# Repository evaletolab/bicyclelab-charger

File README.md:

# 85-110W single output battery charger

This is an opensource lithium-ion battery charger that use laptop power adapter as input.
* Further reading regarding [the bicycle manager](https://github.com/evaletolab/bicyclelab-manager)?

## Features

1. boost input from 18.5V - 4.7A to 42V (or 47.2V) with ~95% of efficiency 
2. stage charging; current control then voltage control
3. full protections: Short circuit / Overload / Over voltage / Over temperature
4. 1 LED indicator for charging status
5. BMS features; Balancing charge on each cell [TODO]
6. custom number of serial cells 5..12
7. small size, only 30x90x8mm

## The result

## Power stage (battery charge)

This if the fourth prototype release. The purpose of this board is to manage the charge  
of a 10/11 serial lithium-ion cell with an input given by a laptop ac adapter (currently the apple magsafe1 85W). 
The software is mainly a PID control based on the MAX_POWER for the fast charge and the BATTERY_VOLTAGE for 
the constant charge. The size of the board is about 30x90mm

## Cell balancing and protection
This project is targeted for each individual cell. The purpose of this project is to make a simple cascading 
module to manage over/under voltage/temperatur for each cell. The first prototype is still not available for testing. 

1. an overvoltage measurement is triggering a passive balancing for the cell
2. TODO - implement an isolated one wire communication to broadcast,
  * undervoltage signal
  * over temperature signal
 
## License
GPL3

Copyright (c) 2012 Olivier Evalet (http://evaletolab.ch/)

Permission is hereby granted, free of charge, to any person obtaining a copy
of this software and associated documentation files (the “Software”), to deal
in the Software without restriction, including without limitation the rights
to use, copy, modify, merge, publish, distribute, sublicense, and/or sell
copies of the Software, and to permit persons to whom the Software is
furnished to do so, subject to the following conditions:

The above copyright notice and this permission notice shall be included in
all copies or substantial portions of the Software.

THE SOFTWARE IS PROVIDED “AS IS”, WITHOUT WARRANTY OF ANY KIND, EXPRESS OR
IMPLIED, INCLUDING BUT NOT LIMITED TO THE WARRANTIES OF MERCHANTABILITY,
FITNESS FOR A PARTICULAR PURPOSE AND NONINFRINGEMENT. IN NO EVENT SHALL THE
AUTHORS OR COPYRIGHT HOLDERS BE LIABLE FOR ANY CLAIM, DAMAGES OR OTHER
LIABILITY, WHETHER IN AN ACTION OF CONTRACT, TORT OR OTHERWISE, ARISING FROM,
OUT OF OR IN CONNECTION WITH THE SOFTWARE OR THE USE OR OTHER DEALINGS IN
THE SOFTWARE.

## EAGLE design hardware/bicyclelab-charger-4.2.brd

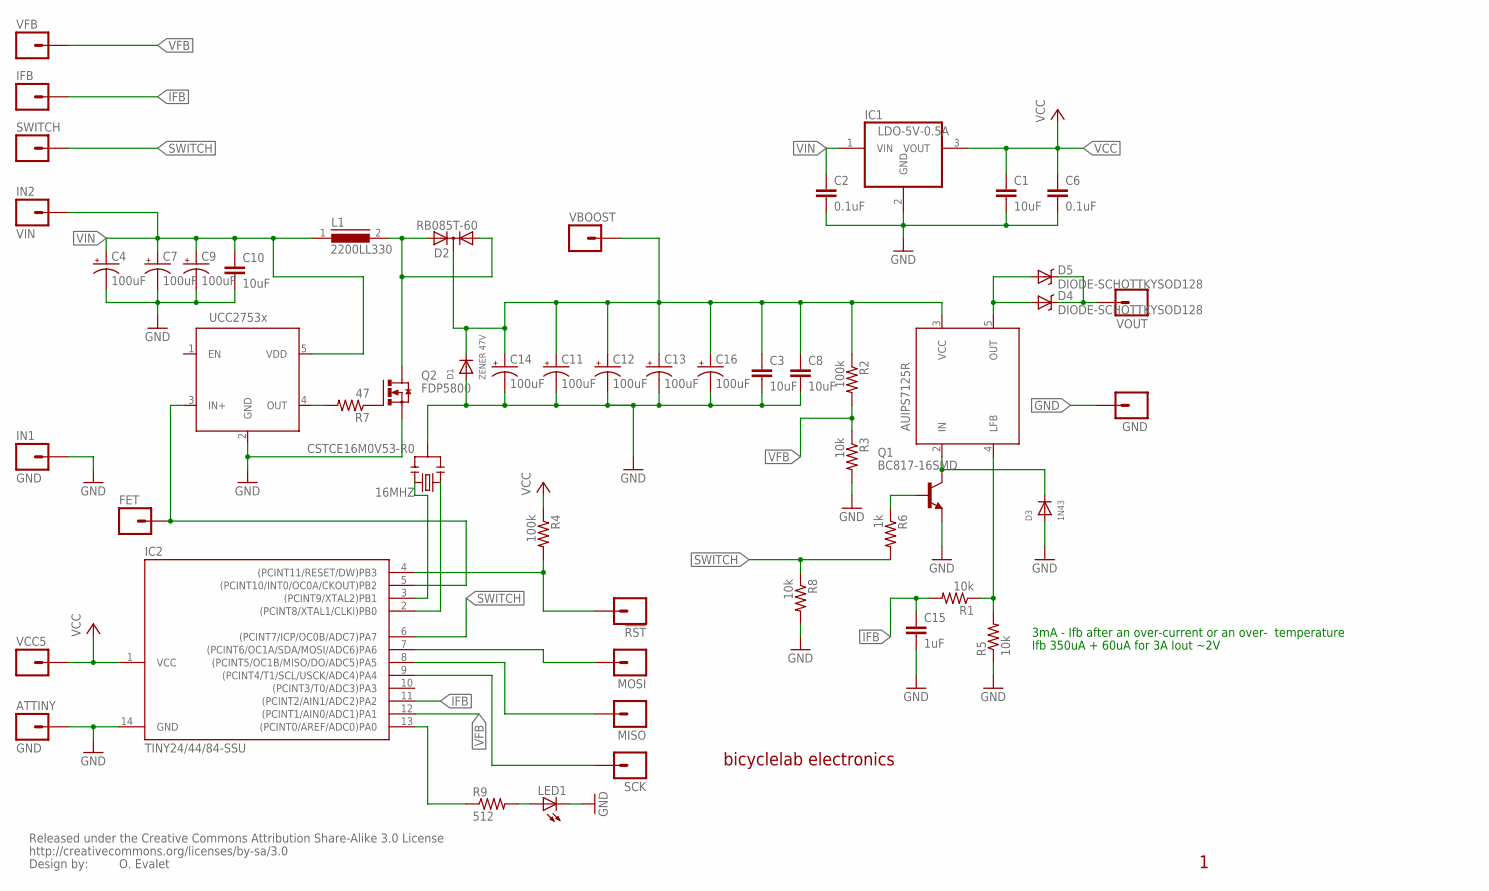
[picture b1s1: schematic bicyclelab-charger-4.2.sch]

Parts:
16MHZ: CSTCE16M0V53-R0; RESONATOR-SMD
!RST: M01SMDNS; 1X01NS
ATTINY: GND; 1X01NS
C1: 10uF; 0805
C2, C6: 0.1uF; 0805
C3, C8, C10: 10uF; 1210
C4, C7, C9, C11, C12, C13, C14, C16: 100uF; PANASONIC_D
C15: 1uF; 0805
D1: ZENER 47V; SOD-123
D2: RB085T-60; TO220AB
D3: 1N43; SOD-123
D4, D5: DIODE-SCHOTTKYSOD128; SOD-128
FET: M01SMDNS; 1X01NS
GND: M01SMDNS; 1X01NS
IC1: LDO-5V-0.5A; SOT223
IC2: TINY24/44/84-SSU; SOIC14
IFB: M01SMDNS; 1X01NS
IN1: GND; 1X01NS
IN2: VIN; 1X01
L1: 2200LL330; DR175
LED1: LEDCHIP-LED0805; CHIP-LED0805
MISO: M01SMDNS; 1X01NS
MOSI: M01SMDNS; 1X01NS
Q1: BC817-16SMD; SOT23-BEC
Q2: FDP5800; TO220AH
R1, R3, R5, R8: 10k; 0805
R2, R4: 100k; 0805
R6: 1k; 0805
R7: 47; 0805
R9: 512; 0805
SCK: M01SMDNS; 1X01NS
SWITCH: M01SMDNS; 1X01NS
U$1: UCC2753XSOT23-6; SOT23-6
U$5: CREATIVE_COMMONS
U$8: AUIPS7125R; DPAK-5
VBOOST: M01SMDNS; 1X01NS
VCC5: M01PTH; 1X01
VFB: M01SMDNS; 1X01NS
VOUT: M01PTH; 1X01

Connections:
GND: 16MHZ.2, ATTINY.1, C1.2, C2.2, C3.2, C4.-, C6.2, C7.-, C8.2, C9.-, C10.2, C11.-, C12.-, C13.-, C14.-, C15.2, C16.-, D1.A, D3.A, GND.1, IC1.2 (GND), IC2.14 (GND), IN1.1, LED1.C, Q1.E, Q2.E (S), R3.2, R5.1, R8.2, U$1.2 (GND)
IFB: C15.1, IC2.11 ((PCINT2/AIN1/ADC2)PA2), IFB.1, R1.2
unnamed: FET.1, IC2.5 ((PCINT10/INT0/OC0A/CKOUT)PB2), U$1.3 (IN+)
unnamed: Q1.B, R6.1
unnamed: !RST.1, IC2.4 ((PCINT11/RESET/DW)PB3), R4.2
unnamed: Q2.B (G), R7.1
unnamed: IC2.7 ((PCINT6/OC1A/SDA/MOSI/ADC6)PA6), MOSI.1
unnamed: IC2.8 ((PCINT5/OC1B/MISO/DO/ADC5)PA5), MISO.1
unnamed: IC2.9 ((PCINT4/T1/SCL/USCK/ADC4)PA4), SCK.1
unnamed: D4.1 (C), D5.1 (C), VOUT.1
unnamed: R1.1, R5.2, U$8.4 (LFB)
unnamed: D3.C, Q1.C, U$8.2 (IN)
unnamed: LED1.A, R9.2
unnamed: IC2.13 ((PCINT0/AREF/ADC0)PA0), R9.1
unnamed: R7.2, U$1.4 (OUT)
unnamed: 16MHZ.3, IC2.3 ((PCINT9/XTAL2)PB1)
unnamed: 16MHZ.1, IC2.2 ((PCINT8/XTAL1/CLKI)PB0)
SWITCH: IC2.6 ((PCINT7/ICP/OC0B/ADC7)PA7), R6.2, R8.1, SWITCH.1
VBOOST: C3.1, C8.1, C11.+, C12.+, C13.+, C14.+, C16.+, D1.C, D2.C, R2.1, U$8.3 (VCC), VBOOST.1
VCC: C1.1, C6.1, IC1.3 (VOUT), IC2.1 (VCC), R4.1, VCC5.1
VFB: IC2.12 ((PCINT1/AIN0/ADC1)PA1), R2.2, R3.1, VFB.1
VFET: D2.A1, D2.A2, L1.2, Q2.C (D)
VIN: C2.1, C4.+, C7.+, C9.+, C10.1, IC1.1 (VIN), IN2.1, L1.1, U$1.5 (VDD)
VOUT: D4.2 (A), D5.2 (A), U$8.5 (OUT)

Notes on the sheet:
bicyclelab electronics
O. Evalet
3mA - Ifb after an over-current or an over- temperature
Ifb 350uA + 60uA for 3A Iout ~2V

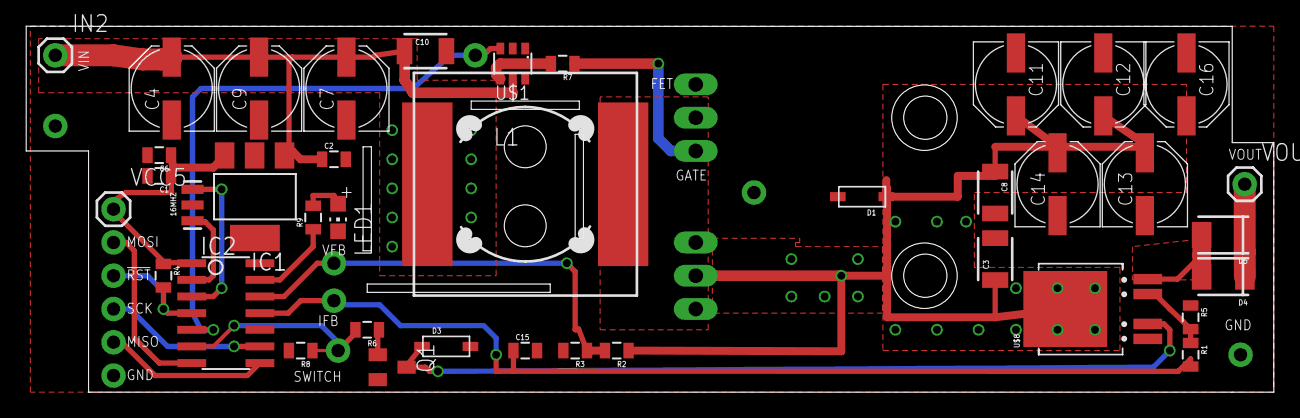
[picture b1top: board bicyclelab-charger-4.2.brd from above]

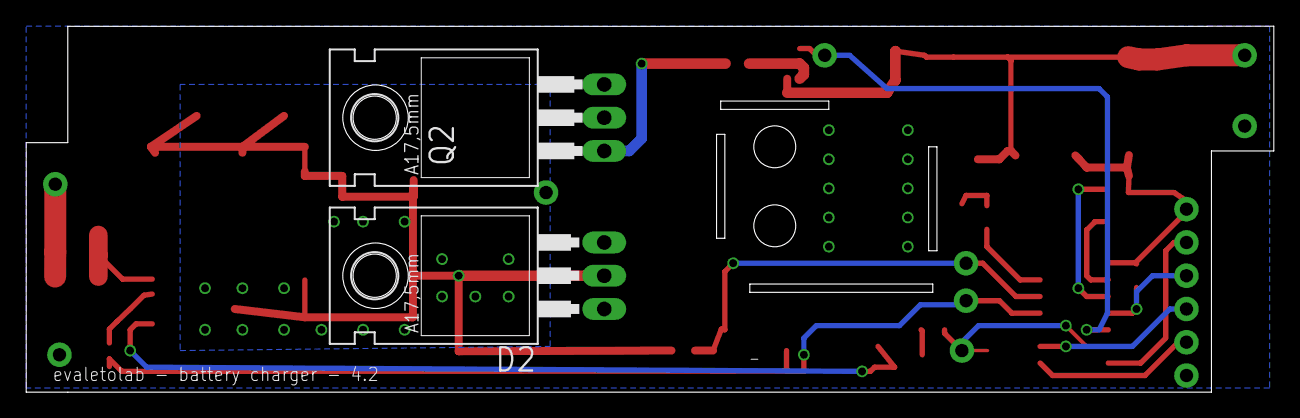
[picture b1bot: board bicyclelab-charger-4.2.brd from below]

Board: 2 copper layers, 95.2 x 27.9 mm, 54 parts (2 on the bottom side), 24 nets.

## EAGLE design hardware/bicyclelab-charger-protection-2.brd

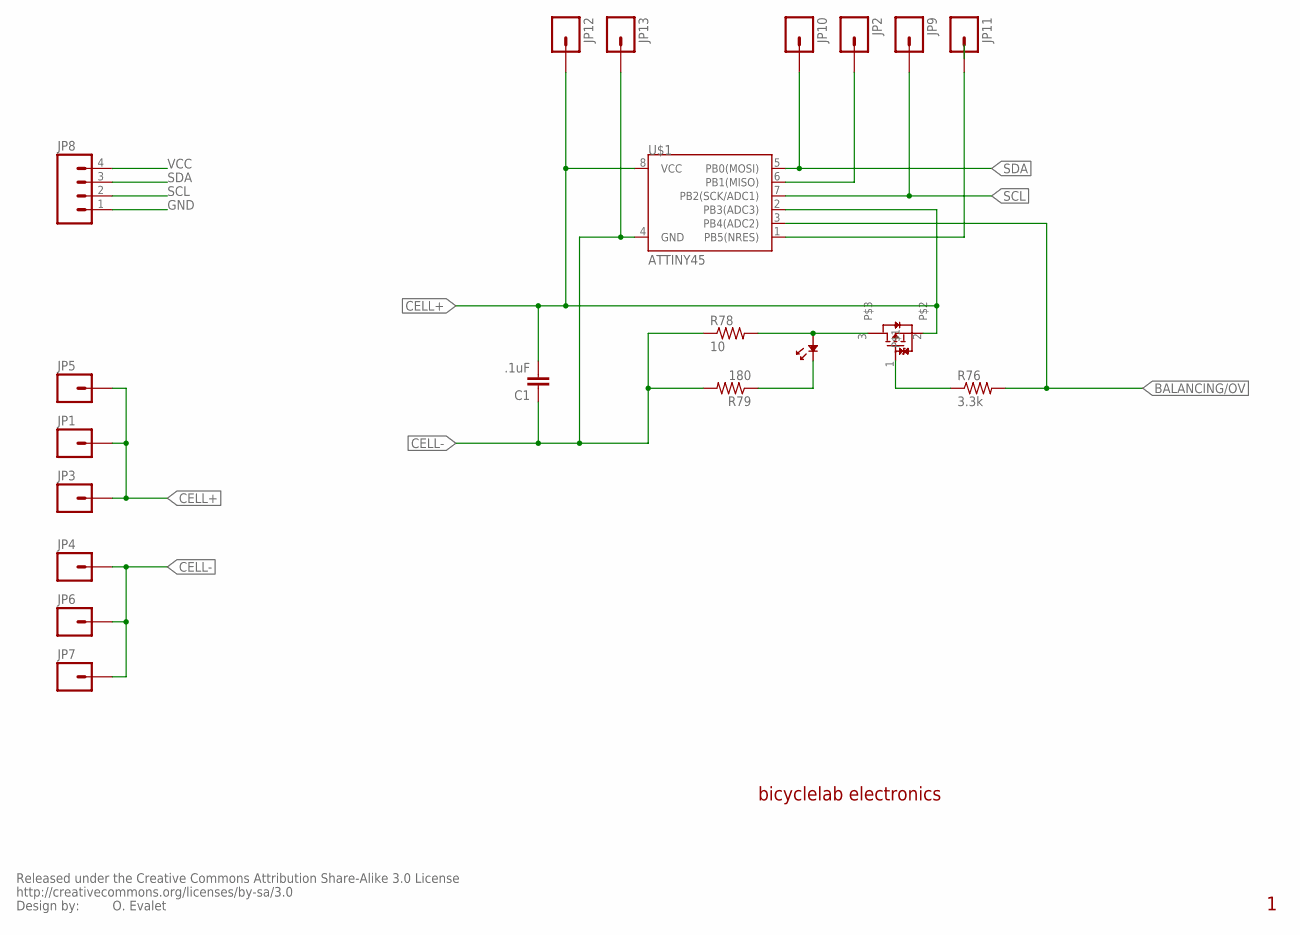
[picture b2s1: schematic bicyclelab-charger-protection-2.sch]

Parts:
C1: .1uF; C0402
JP1, JP3, JP4, JP5, JP6, JP7: M01SMD-4.5X1.5; PAD-1.5X4.5
JP2, JP9, JP10, JP11, JP12, JP13: M01SMD-TINY; PAD-SMD
JP8: M04PTH; 1X04
LED12: LED-0805; 0805
R76: 3.3k; R0805
R78: 10; R2512
R79: 180; R0805
T12: RTR020P02; TSMT3
U$1: ATTINY45; SO08-EIAJ
U$5: CREATIVE_COMMONS

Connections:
BALANCING/OV: R76.2, U$1.3 (PB4(ADC2))
CELL+: C1.2, JP1.P$1, JP3.P$1, JP5.P$1, JP12.P$1, T12.2, U$1.2 (PB3(ADC3)), U$1.8 (VCC)
CELL-: C1.1, JP4.P$1, JP6.P$1, JP7.P$1, JP13.P$1, R78.1, R79.2, U$1.4 (GND)
GND: JP8.1
unnamed: JP2.P$1, U$1.6 (PB1(MISO))
unnamed: JP11.P$1, U$1.1 (PB5(NRES))
unnamed: LED12.P$2, R78.2, T12.3
unnamed: LED12.P$1, R79.1
unnamed: R76.1, T12.1
SCL: JP8.2, JP9.P$1, U$1.7 (PB2(SCK/ADC1))
SDA: JP8.3, JP10.P$1, U$1.5 (PB0(MOSI))
VCC: JP8.4

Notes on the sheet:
bicyclelab electronics
O. Evalet

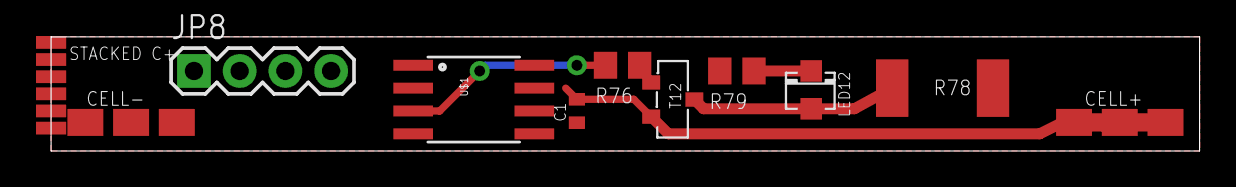
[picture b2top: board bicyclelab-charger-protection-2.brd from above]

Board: 2 copper layers, 63.8 x 6.3 mm, 21 parts (0 on the bottom side), 10 nets.

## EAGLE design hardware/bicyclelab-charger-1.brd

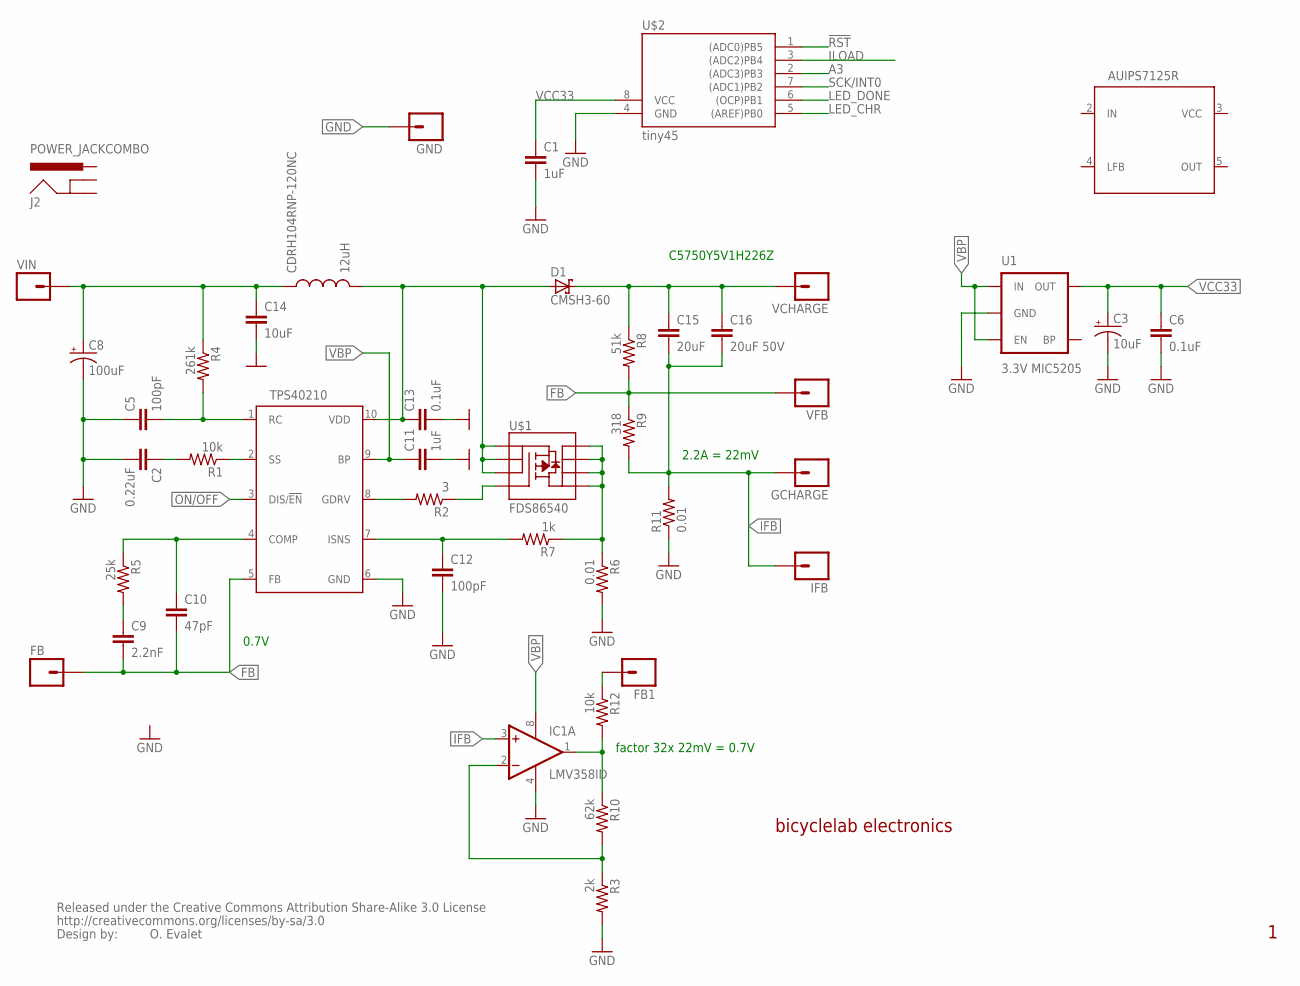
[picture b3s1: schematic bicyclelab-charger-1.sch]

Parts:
11: TPS40211; MSOP-10-GNDPAD
C1, C11: 1uF; 0402-CAP
C2: 0.22uF; 0402-CAP
C3: 10uF; EIA3216
C5, C12: 100pF; 0402-CAP
C6: 0.1uF; 0603-CAP
C8: 100uF; PANASONIC_C
C9: 2.2nF; 0402-CAP
C10: 47pF; 0402-CAP
C13: 0.1uF; 0402-CAP
C14: 10uF; 1206
C15: 20uF; C2220K
C16: 20uF 50V; C2220K
CDRH104RNP-120NC: 12uH; CR75
D1: CMSH3-60; SMC
FB, FB1: M01SMDNS; 1X01NS
GCHARGE: M01SMDNS; 1X01NS
GND: M01SMDNS; 1X01NS
IC1: LMV358ID; SO08
IFB: M01SMDNS; 1X01NS
J2: POWER_JACKCOMBO; POWER_JACK_COMBO
R1, R12: 10k; 0402-RES
R2: 3; 0402-RES
R3: 2k; 0402-RES
R4: 261k; 0402-RES
R5: 25k; 0402-RES
R6, R11: 0.01; 0402-RES
R7: 1k; 0402-RES
R8: 51k; 0402-RES
R9: 318; 0402-RES
R10: 62k; 0402-RES
U1: 3.3V MIC5205; SOT23-5
U$1: FDS86540; SO08
U$2: tiny45; SOIC8
U$5: CREATIVE_COMMONS
U$8: AUIPS7125R; DPAK-5
VCHARGE: M01SMDNS; 1X01NS
VFB: M01SMDNS; 1X01NS
VIN: M01SMDNS; 1X01NS

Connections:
!RST: U$2.1 ((ADC0)PB5)
A3: U$2.2 ((ADC3)PB3)
FB: 11.5 (FB), C9.2, C10.2, FB.1, R8.2, R9.1, VFB.1
FB1: IC1.1 (OUT), R10.1, R12.2
GND: 11.6 (GND), C1.2, C2.2, C3.C (-), C5.1, C6.2, C8.-, C11.2, C12.2, C13.2, C14.2, GND.1, IC1.4 (V-), R3.2, R6.2, R11.1, U1.2 (GND), U$2.4 (GND)
IFB: C15.2, C16.2, GCHARGE.1, IC1.3 (+IN), IFB.1, R9.2, R11.2
ILOAD: U$2.3 ((ADC2)PB4)
LED_CHR: U$2.5 ((AREF)PB0)
LED_DONE: U$2.6 ((OCP)PB1)
unnamed: C8.+, C14.1, CDRH104RNP-120NC.P$1 (1), R4.1, VIN.1
unnamed: 11.1 (RC), C5.2, R4.2
unnamed: 11.2 (SS), R1.1
unnamed: C2.1, R1.2
unnamed: R2.1, U$1.4 (G)
unnamed: C15.1, C16.1, D1.C, R8.1, VCHARGE.1
unnamed: 11.8 (GDRV), R2.2
unnamed: 11.4 (COMP), C10.1, R5.1
unnamed: C9.1, R5.2
unnamed: FB1.1, R12.1
unnamed: 11.10 (VDD), C13.1, CDRH104RNP-120NC.P$2 (2), D1.A, U$1.1 (S), U$1.2 (S), U$1.3 (S)
unnamed: R6.1, R7.1, U$1.5 (D), U$1.6 (D), U$1.7 (D), U$1.8 (D)
unnamed: 11.7 (ISNS), C12.1, R7.2
unnamed: IC1.2 (-IN), R3.1, R10.2
ON/OFF: 11.3 (DIS/!EN)
SCK/INT0: U$2.7 ((ADC1)PB2)
VBP: 11.9 (BP), C11.1, IC1.8 (V+), U1.1 (IN), U1.3 (EN)
VCC33: C1.1, C3.A (+), C6.1, U1.5 (OUT), U$2.8 (VCC)

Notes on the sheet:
bicyclelab electronics
O. Evalet
C5750Y5V1H226Z
0.7V
2.2A = 22mV
factor 32x 22mV = 0.7V

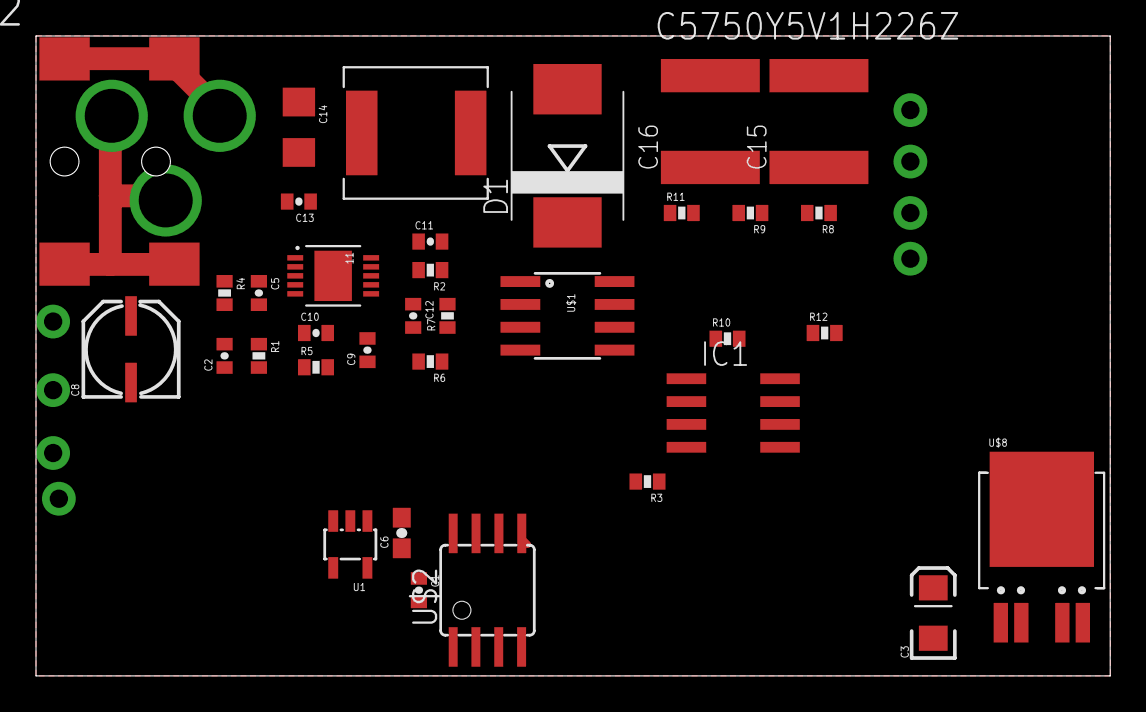
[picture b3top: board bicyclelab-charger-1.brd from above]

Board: 2 copper layers, 59.7 x 35.5 mm, 44 parts (0 on the bottom side), 20 nets.

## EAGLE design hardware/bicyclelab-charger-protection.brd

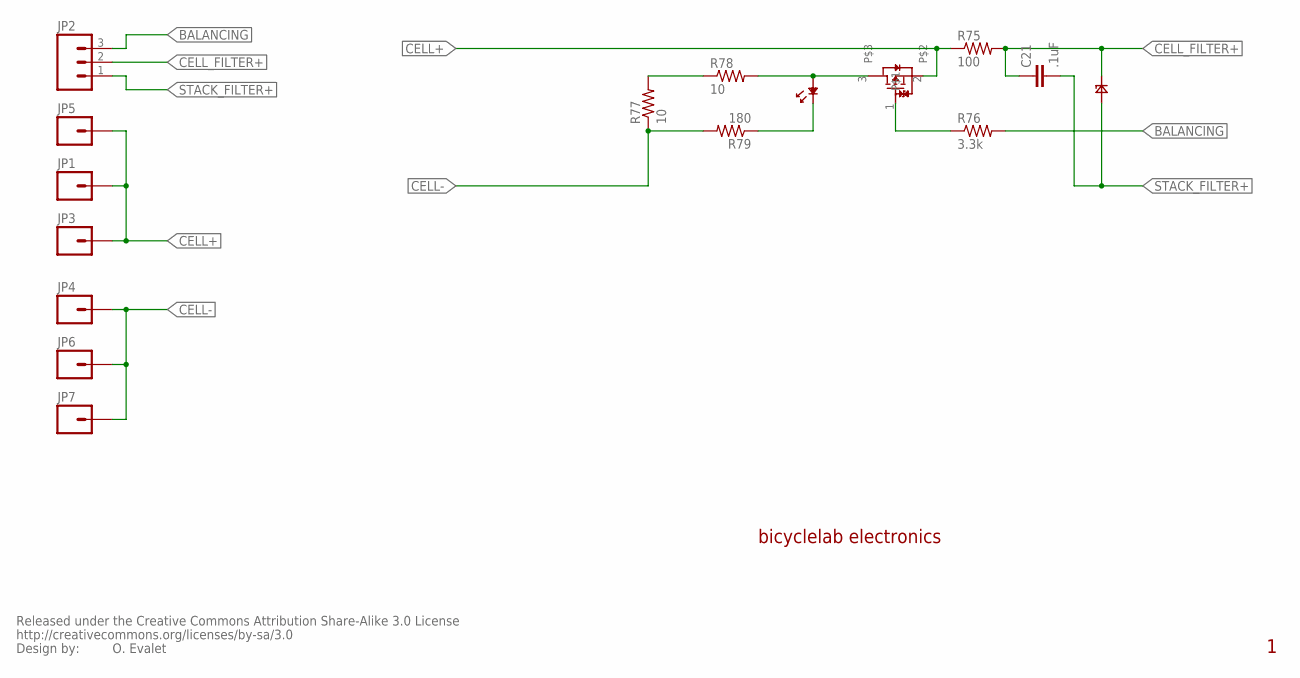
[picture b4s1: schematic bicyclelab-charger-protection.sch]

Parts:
C21: .1uF; C0402
JP1, JP3, JP4, JP5, JP6, JP7: M01SMD-4.5X1.5; PAD-1.5X4.5
JP2: M03PTH; 1X03
LED12: LED-0805; 0805
PD12: PDZ7.5B; SOD323
R75: 100; R0402
R76: 3.3k; R0402
R77, R78: 10; R2512
R79: 180; R0805
T12: RTR020P02; TSMT3
U$5: CREATIVE_COMMONS

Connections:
BALANCING: JP2.3, R76.2
CELL+: JP1.P$1, JP3.P$1, JP5.P$1, R75.1, T12.2
CELL-: JP4.P$1, JP6.P$1, JP7.P$1, R77.1, R79.2
CELL_FILTER+: C21.1, JP2.2, PD12.P$1, R75.2
unnamed: R77.2, R78.1
unnamed: LED12.P$2, R78.2, T12.3
unnamed: LED12.P$1, R79.1
unnamed: R76.1, T12.1
STACK_FILTER+: C21.2, JP2.1, PD12.P$2

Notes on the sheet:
bicyclelab electronics
O. Evalet

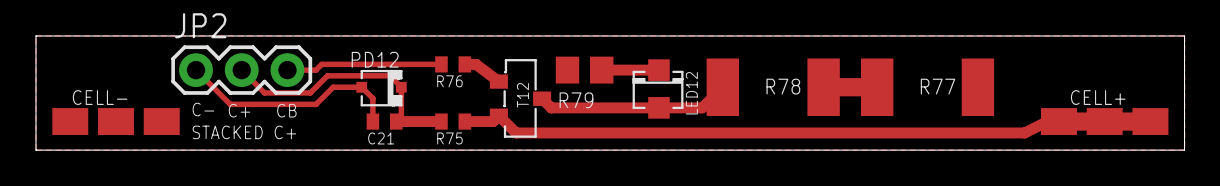
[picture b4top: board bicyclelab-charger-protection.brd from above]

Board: 2 copper layers, 63.8 x 6.3 mm, 17 parts (0 on the bottom side), 9 nets.

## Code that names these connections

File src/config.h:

/**
 * battery life calculator
 * http://oregonembedded.com/batterycalc.htm
 */

#ifndef CONFIG_H_
#define CONFIG_H_

#define CONFIG_WITH_DEBUG
#define CONFIG_WITH_I2C
#define CONFIG_WITH_ECLIPSE
//#define CONFIG_WITH_LOGGER
//#define CONFIG_WITH_TIMER

// divide clock
#if F_CPU == 16000000L
#	define SET_PRESCALER 1
#elif F_CPU == 8000000L
#	define SET_PRESCALER 0
#endif

// Disabled EEPROM when debugging
// DEBUG CHANNEL ATTINYX5,
// if (F_CPU <= 8000000L) => port B bit 3 (PB3:4) ELSE port B bit 2 (PB2:5)
// DEBUG CHANNEL ATTINYX4,
// if (F_CPU <= 8000000L) => port B bit 0 (PB0:2) ELSE port A bit 0 (PA0:13)
#ifdef DEBUG_SERIAL
#  define CONFIG_WITH_PRINT
#else
#	define CONFIG_WITH_EEPROM
#endif

#define         PRINT_TICK 200
#define         TIMER_TICK 10
#define         TIMER_WAIT 100000/2
#define         PRINT 1

#define  V2B(V)  (V*1023.0/VCC_REF)


#if defined( __AVR_ATtinyX4__ )


// ATMEL ATTINY84 / ARDUINO
//
//                           +-\/-+
//                     VCC  1|    |14  GND
//  (Serial1)  (D  0)  PB0  2|    |13  AREF (D 10)       (Serial2)
//             (D  1)  PB1  3|    |12  PA1  (D  9) 
//                     PB3  4|    |11  PA2  (D  8) 
//  PWM  INT0  (D  2)  PB2  5|    |10  PA3  (D  7) 
//  PWM        (D  3)  PA7  6|    |9   PA4  (D  6) 
//  PWM        (D  4)  PA6  7|    |8   PA5  (D  5)        PWM (Serial3)
//                           +----+


#define         P_PWM 5
#define         P_SW 6
#define         P_VCC5 7
#define         A_VFB 1
#define         A_IFB 2

#define TEMPERATURE_CALIBRATE 294

// 0x22 => TEMP sensor, 0x80 1.1V reference
# define A_TEMP 0xA2
//1.1V VREF MUX100001
# define MUX_VREF 0b00100001
//VCC as voltage reference _BT(REFS0)
# define ADC_VREF 0b00000000

#elif defined( __AVR_ATtinyX5__ )

// ATMEL ATTINY45 / ARDUINO
//
//                           +-\/-+
//  Ain0 !RST  (D  5)  PB5  1|    |8   VCC
//  Ain3       (D  3)  PB3  2|    |7   PB2  (D  2)  INT0  Ain1 SCK
//  Ain2       (D  4)  PB4  3|    |6   PB1  (D  1)        pwm1 MISO
//                     GND  4|    |5   PB0  (D  0)        pwm0 MOSI
//                           +----+


#define TEMPERATURE_CALIBRATE 294
// 0x0F => TEMP sensor, 0x80 1.1V reference
# define A_TEMP 0x8F
//1.1V VREF
# define MUX_VREF 0b00001100
//VCC as voltage reference
# define ADC_VREF 0b00000000

#else
//
// ARDUINO 

// Set pin 6's PWM frequency to 62500 Hz (62500/1 = 62500)
// Note that the base frequency for pins 5 and 6 is 62500 Hz  
// *   - Changes on pins 3, 5, 6, or 11 may cause the delay() and
// *     millis() functions to stop working. Other timing-related
#define         P_PWM 5
#define         P_SW 2
#define         P_VCC5 8
#define         A_VFB 0
#define         A_IFB 1

#endif



#endif

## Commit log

2012-10-07 Create gh-pages branch via GitHub
2012-10-07 release
2013-07-31 first devel board v0.1
2013-08-18 implement code for tiny and arduino, check Makefile.p328
2013-09-06 clean refactoring of latest tested implementation
2013-09-11 90% eff. @70W, it rocks
2013-09-20 refactor charger code
2013-09-27 prototype is working now. did some adjustement as fine tunning
2013-09-27 power prototype is working now. did some adjustement as fine tunning

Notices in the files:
parts and their libraries:
SparkFun: Released under the Creative Commons Attribution Share-Alike 3.0 License
SparkFun: http://creativecommons.org/licenses/by-sa/3.0
